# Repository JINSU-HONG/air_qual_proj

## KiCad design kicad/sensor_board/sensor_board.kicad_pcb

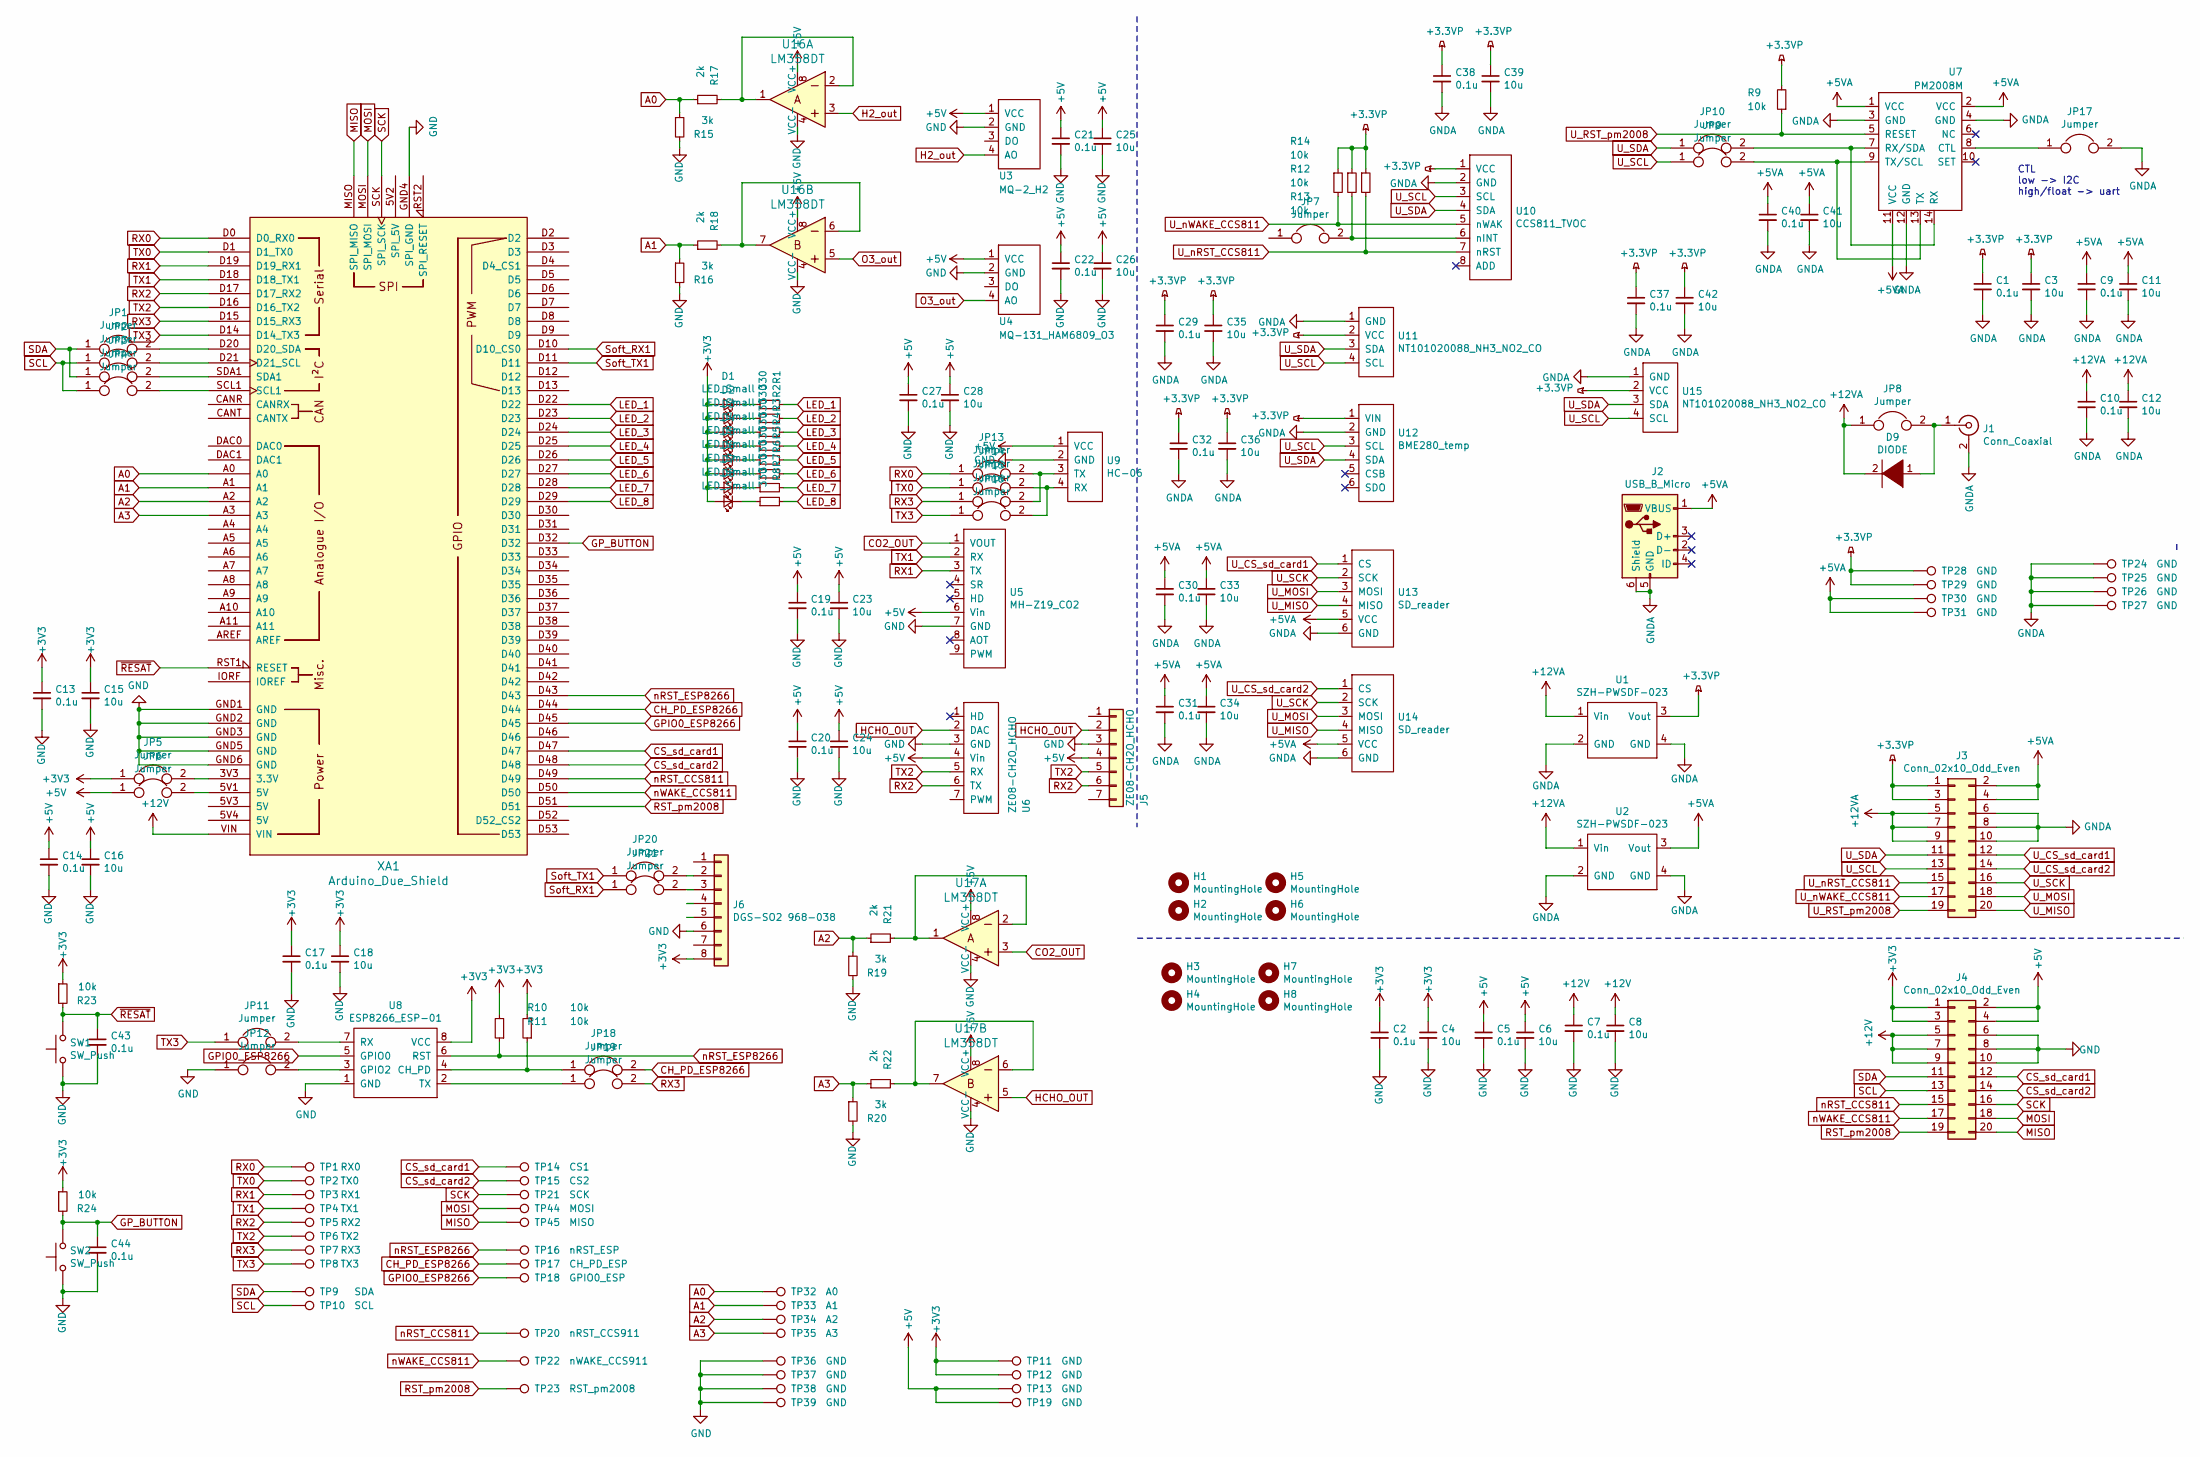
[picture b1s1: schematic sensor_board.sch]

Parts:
C1, C2, C5, C7, C9, C10, C13, C14, C17, C19, C20, C21, C22, C27, C29, C30, C31, C32, C37, C38, C40, C43, C44: 0.1u; C_0805_2012Metric_Pad1.15x1.40mm_HandSolder
C3, C4, C6, C8, C11, C12, C15, C16, C18, C23, C24, C25, C26, C28, C33, C34, C35, C36, C39, C41, C42: 10u; C_0805_2012Metric_Pad1.15x1.40mm_HandSolder
D1, D2, D3, D4, D5, D6, D7, D8: LED_Small; D_0805_2012Metric_Pad1.15x1.40mm_HandSolder
D9: DIODE; D_SMA_Handsoldering
H1, H2, H3, H4, H5, H6, H7, H8: MountingHole; MountingHole_3.2mm_M3
J1: Conn_Coaxial; BarrelJack_Horizontal
J2: USB_B_Micro; USB_Micro_B_Male_UJ2-MIBH-4-SMT-TR
J3, J4: Conn_02x10_Odd_Even; PinHeader_2x10_P2.54mm_Vertical
J5: ZE08-CH2O_HCHO; PinSocket_1x07_P2.54mm_Vertical
J6: DGS-SO2 968-038; PinHeader_1x08_P2.54mm_Horizontal
JP1, JP2, JP3, JP4, JP5, JP6, JP7, JP8, JP9, JP10, JP11, JP12, JP13, JP14, JP15, JP16, JP17, JP18, JP19, JP20, JP21: Jumper; PinHeader_1x02_P2.54mm_Vertical
R1, R2, R3, R4, R5, R6, R7, R8: 330; R_0805_2012Metric_Pad1.15x1.40mm_HandSolder
R9, R10, R11, R12, R13, R14, R23, R24: 10k; R_0805_2012Metric_Pad1.15x1.40mm_HandSolder
R15, R16, R19, R20: 3k; R_0805_2012Metric_Pad1.15x1.40mm_HandSolder
R17, R18, R21, R22: 2k; R_0805_2012Metric_Pad1.15x1.40mm_HandSolder
SW1, SW2: SW_Push; SW_SPST_TL3305A
TP1: RX0; PinHeader_1x01_P2.54mm_Vertical
TP2: TX0; PinHeader_1x01_P2.54mm_Vertical
TP3: RX1; PinHeader_1x01_P2.54mm_Vertical
TP4: TX1; PinHeader_1x01_P2.54mm_Vertical
TP5: RX2; PinHeader_1x01_P2.54mm_Vertical
TP6: TX2; PinHeader_1x01_P2.54mm_Vertical
TP7: RX3; PinHeader_1x01_P2.54mm_Vertical
TP8: TX3; PinHeader_1x01_P2.54mm_Vertical
TP9: SDA; PinHeader_1x01_P2.54mm_Vertical
TP10: SCL; PinHeader_1x01_P2.54mm_Vertical
TP11, TP12, TP13, TP19, TP24, TP25, TP26, TP27, TP28, TP29, TP30, TP31, TP36, TP37, TP38, TP39: GND; PinHeader_1x01_P2.54mm_Vertical
TP14: CS1; PinHeader_1x01_P2.54mm_Vertical
TP15: CS2; PinHeader_1x01_P2.54mm_Vertical
TP16: nRST_ESP; PinHeader_1x01_P2.54mm_Vertical
TP17: CH_PD_ESP; PinHeader_1x01_P2.54mm_Vertical
TP18: GPIO0_ESP; PinHeader_1x01_P2.54mm_Vertical
TP20: nRST_CCS911; PinHeader_1x01_P2.54mm_Vertical
TP21: SCK; PinHeader_1x01_P2.54mm_Vertical
TP22: nWAKE_CCS911; PinHeader_1x01_P2.54mm_Vertical
TP23: RST_pm2008; PinHeader_1x01_P2.54mm_Vertical
TP32: A0; PinHeader_1x01_P2.54mm_Vertical
TP33: A1; PinHeader_1x01_P2.54mm_Vertical
TP34: A2; PinHeader_1x01_P2.54mm_Vertical
TP35: A3; PinHeader_1x01_P2.54mm_Vertical
TP44: MOSI; PinHeader_1x01_P2.54mm_Vertical
TP45: MISO; PinHeader_1x01_P2.54mm_Vertical
U1, U2: SZH-PWSDF-023
U3: MQ-2_H2; MQ-2
U4: MQ-131_HAM6809_O3; MQ-131
U5: MH-Z19_CO2; MH-Z19
U6: ZE08-CH2O_HCHO; ZE08-CH2O
U7: PM2008M; pm2008m
U8: ESP8266_ESP-01; esp8266_ESP-01
U9: HC-06
U10: CCS811_TVOC; CCS811
U11, U15: NT101020088_NH3_NO2_CO; NT101020088
U12: BME280_temp; BME280
U13, U14: SD_reader
U16, U17: LM358DT; SOIC-8_W3.9mm; MPN LM358DT; Digi-Key_PN 497-1591-1-ND
XA1: Arduino_Due_Shield

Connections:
+3.3VP: C1.1, C3.1, C29.1, C32.1, C35.1, C36.1, C37.1, C38.1, C39.1, C42.1, J3.1, J3.3, R9.2, R12.1, R13.1, R14.1, TP28.1, TP29.1, U1.3 (Vout), U10.1 (VCC), U11.2 (VCC), U12.1 (VIN), U15.2 (VCC)
+3V3: C2.1, C4.1, C13.1, C15.1, C17.1, C18.1, D1.2 (A), D2.2 (A), D3.2 (A), D4.2 (A), D5.2 (A), D6.2 (A), D7.2 (A), D8.2 (A), J4.1, J4.3, J6.8, JP5.1, R10.2, R11.2, R23.1, R24.1, TP11.1, TP12.1, U8.8 (VCC)
+5V: C5.1, C6.1, C14.1, C16.1, C19.1, C20.1, C21.1, C22.1, C23.1, C24.1, C25.1, C26.1, C27.1, C28.1, J4.2, J4.4, J5.4, JP6.1, TP13.1, TP19.1, U3.1 (VCC), U4.1 (VCC), U5.6 (Vin), U6.4 (Vin), U9.1 (VCC), U16.8 (VCC+), U17.8 (VCC+)
+5VA: C9.1, C11.1, C30.1, C31.1, C33.1, C34.1, C40.1, C41.1, J2.1 (VBUS), J3.2, J3.4, TP30.1, TP31.1, U2.3 (Vout), U7.1 (VCC), U7.2 (VCC), U7.11 (VCC), U13.5 (VCC), U14.5 (VCC)
+12V: C7.1, C8.1, J4.5, J4.7, J4.9, XA1.VIN
+12VA: C10.1, C12.1, D9.2 (A), J3.5, J3.7, J3.9, JP8.1, U1.1 (Vin), U2.1 (Vin)
A0: R15.1, R17.1, TP32.1, XA1.A0
A1: R16.1, R18.1, TP33.1, XA1.A1
A2: R19.1, R21.1, TP34.1, XA1.A2
A3: R20.1, R22.1, TP35.1, XA1.A3
CH_PD_ESP8266: JP18.2, TP17.1, XA1.D44
CO2_OUT: U5.1 (VOUT), U17.3
CS_sd_card1: J4.12, TP14.1, XA1.D47
CS_sd_card2: J4.14, TP15.1, XA1.D48
GND: C2.2, C4.2, C5.2, C6.2, C7.2, C8.2, C13.2, C14.2, C15.2, C16.2, C17.2, C18.2, C19.2, C20.2, C21.2, C22.2, C23.2, C24.2, C25.2, C26.2, C27.2, C28.2, C43.2, C44.2, J4.6, J4.8, J4.10, J5.3, J6.6, JP12.1, R15.2, R16.2, R19.2, R20.2, SW1.1, SW2.1, TP36.1, TP37.1, TP38.1, TP39.1, U3.2 (GND), U4.2 (GND), U5.7 (GND), U6.3 (GND), U8.1 (GND), U9.2 (GND), U16.4 (VCC-), U17.4 (VCC-), XA1.GND1 (GND), XA1.GND2 (GND), XA1.GND3 (GND), XA1.GND4 (SPI_GND), XA1.GND5 (GND), XA1.GND6 (GND)
GNDA: C1.2, C3.2, C9.2, C10.2, C11.2, C12.2, C29.2, C30.2, C31.2, C32.2, C33.2, C34.2, C35.2, C36.2, C37.2, C38.2, C39.2, C40.2, C41.2, C42.2, J1.2 (Ext), J2.5 (GND), J2.6 (Shield), J3.6, J3.8, J3.10, JP17.2, TP24.1, TP25.1, TP26.1, TP27.1, U1.2 (GND), U1.4 (GND), U2.2 (GND), U2.4 (GND), U7.3 (GND), U7.4 (GND), U7.12 (GND), U10.2 (GND), U11.1 (GND), U12.2 (GND), U13.6 (GND), U14.6 (GND), U15.1 (GND)
GPIO0_ESP8266: TP18.1, U8.5 (GPIO0), XA1.D45
GP_BUTTON: C44.1, R24.2, SW2.2, XA1.D32
H2_out: U3.4 (AO), U16.3
HCHO_OUT: J5.2, U6.2 (DAC), U17.5
LED_1: R1.2, XA1.D22
LED_2: R2.2, XA1.D23
LED_3: R3.2, XA1.D24
LED_4: R4.2, XA1.D25
LED_5: R5.2, XA1.D26
LED_6: R6.2, XA1.D27
LED_7: R7.2, XA1.D28
LED_8: R8.2, XA1.D29
MISO: J4.20, TP45.1, XA1.MISO (SPI_MISO)
MOSI: J4.18, TP44.1, XA1.MOSI (SPI_MOSI)
unnamed: D1.1 (K), R1.1
unnamed: D2.1 (K), R2.1
unnamed: D3.1 (K), R3.1
unnamed: D4.1 (K), R4.1
unnamed: D5.1 (K), R5.1
unnamed: D6.1 (K), R6.1
unnamed: D7.1 (K), R7.1
unnamed: D8.1 (K), R8.1
unnamed: D9.1 (K), J1.1 (In), JP8.2
unnamed: J6.2, JP20.2
unnamed: J6.3, JP21.2
unnamed: JP1.2, XA1.D20 (D20_SDA)
unnamed: JP2.2, XA1.D21 (D21_SCL)
unnamed: JP3.2, XA1.SDA1
unnamed: JP4.2, XA1.SCL1
unnamed: JP5.2, XA1.3V3 (3.3V)
unnamed: JP6.2, XA1.5V1 (5V)
unnamed: JP7.2, R13.2, U10.6 (nINT)
unnamed: JP9.2, U7.9 (TX/SCL), U7.13 (TX)
unnamed: JP10.2, U7.7 (RX/SDA), U7.14 (RX)
unnamed: JP11.2, U8.7 (RX)
unnamed: JP12.2, U8.3 (GPIO2)
unnamed: JP13.2, JP15.2, U9.3 (TX)
unnamed: JP14.2, JP16.2, U9.4 (RX)
unnamed: JP17.1, U7.8 (CTL)
unnamed: JP18.1, R11.1, U8.4 (CH_PD)
unnamed: JP19.1, U8.2 (TX)
unnamed: R17.2, U16.1, U16.2
unnamed: R18.2, U16.6, U16.7
unnamed: R21.2, U17.1, U17.2
unnamed: R22.2, U17.6, U17.7
O3_out: U4.4 (AO), U16.5
RST_pm2008: J4.19, TP23.1, XA1.D51
RX0: JP13.1, TP1.1, XA1.D0 (D0_RX0)
RX1: TP3.1, U5.3 (TX), XA1.D19 (D19_RX1)
RX2: J5.6, TP5.1, U6.6 (TX), XA1.D17 (D17_RX2)
RX3: JP15.1, JP19.2, TP7.1, XA1.D15 (D15_RX3)
SCK: J4.16, TP21.1, XA1.SCK (SPI_SCK)
SCL: J4.13, JP2.1, JP4.1, TP10.1
SDA: J4.11, JP1.1, JP3.1, TP9.1
Soft_RX1: JP21.1, XA1.D10 (D10_CS0)
Soft_TX1: JP20.1, XA1.D11
TX0: JP14.1, TP2.1, XA1.D1 (D1_TX0)
TX1: TP4.1, U5.2 (RX), XA1.D18 (D18_TX1)
TX2: J5.5, TP6.1, U6.5 (RX), XA1.D16 (D16_TX2)
TX3: JP11.1, JP16.1, TP8.1, XA1.D14 (D14_TX3)
U_CS_sd_card1: J3.12, U13.1 (CS)
U_CS_sd_card2: J3.14, U14.1 (CS)
U_MISO: J3.20, U13.4 (MISO), U14.4 (MISO)
U_MOSI: J3.18, U13.3 (MOSI), U14.3 (MOSI)
U_RST_pm2008: J3.19, R9.1, U7.5 (RESET)
U_SCK: J3.16, U13.2 (SCK), U14.2 (SCK)
U_SCL: J3.13, JP9.1, U10.3 (SCL), U11.4 (SCL), U12.3 (SCL), U15.4 (SCL)
U_SDA: J3.11, JP10.1, U10.4 (SDA), U11.3 (SDA), U12.4 (SDA), U15.3 (SDA)
U_nRST_CCS811: J3.15, R14.2, U10.7 (nRST)
U_nWAKE_CCS811: J3.17, R12.2, U10.5 (nWAK)
nRST_CCS811: J4.15, TP20.1, XA1.D49
nRST_ESP8266: R10.1, TP16.1, U8.6 (RST), XA1.D43
nWAKE_CCS811: J4.17, TP22.1, XA1.D50
~RESAT: C43.1, R23.2, SW1.2, XA1.RST1 (RESET)

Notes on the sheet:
CTL low -> I2C high/float -> uart

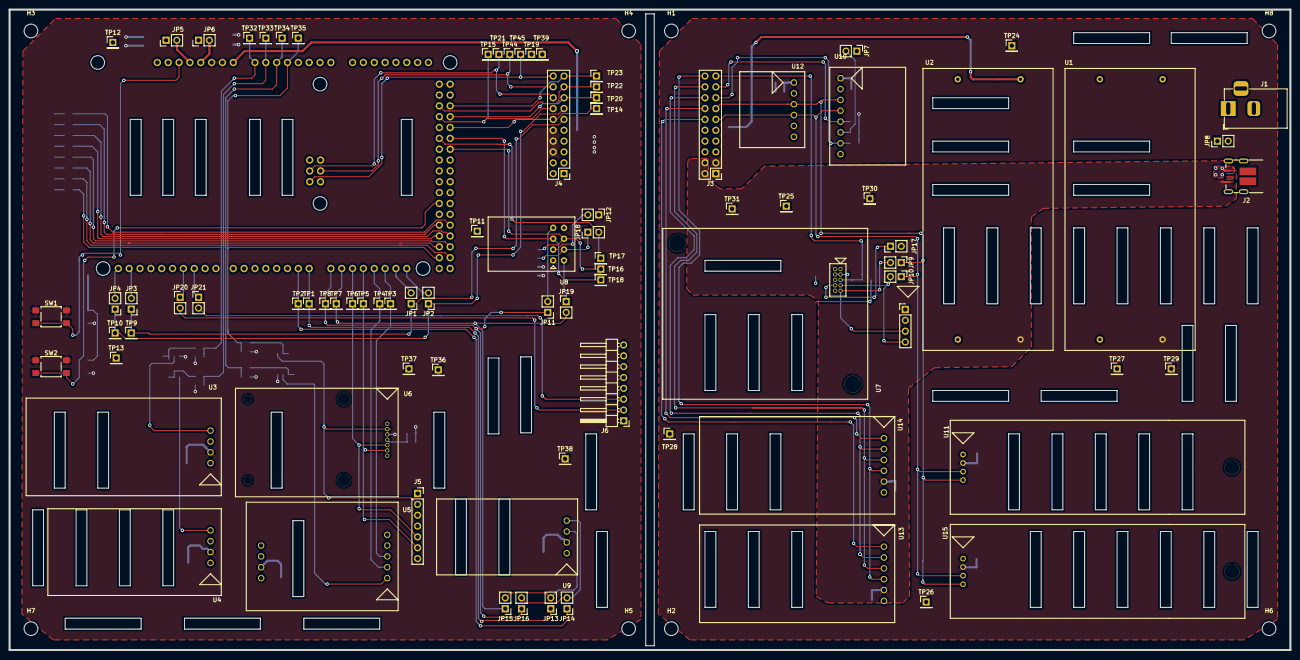
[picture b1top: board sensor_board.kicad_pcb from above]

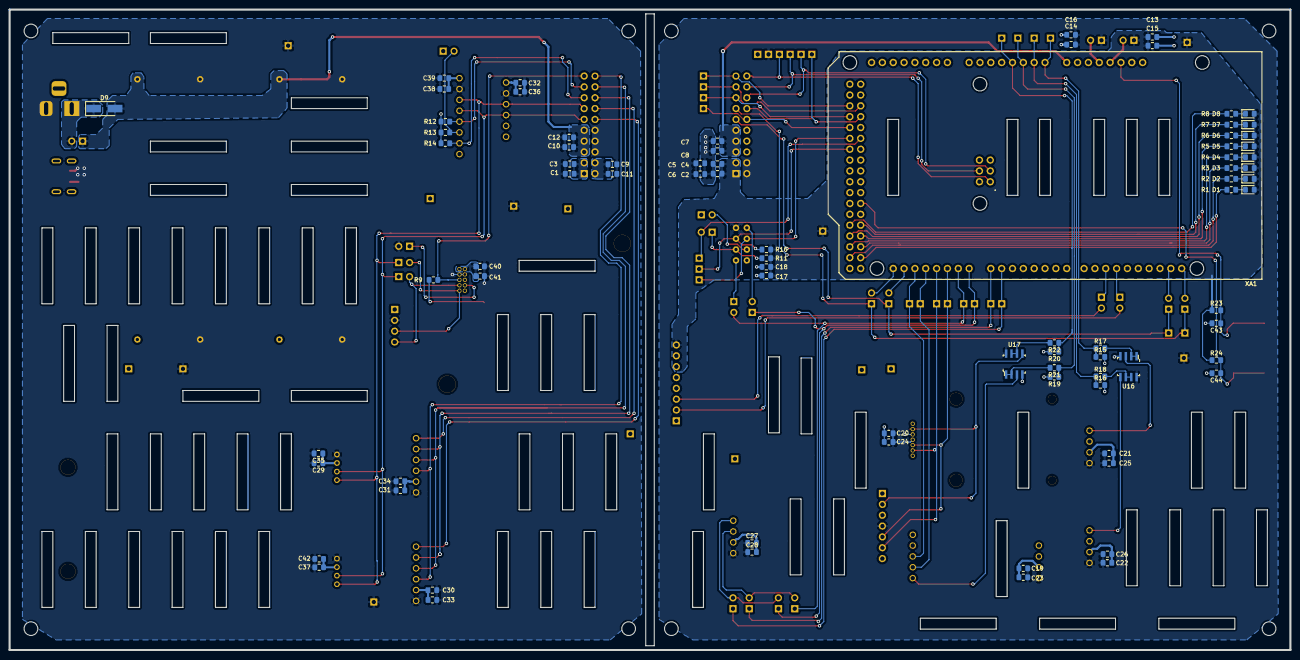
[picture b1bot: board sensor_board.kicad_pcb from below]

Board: 2 copper layers, 300.0 x 150.0 mm, 173 parts (80 on the bottom side), 90 nets.

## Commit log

2020-04-04 all all file
